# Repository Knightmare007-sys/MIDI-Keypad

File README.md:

# MIDI-Keypad
A small controller with keys that does not make sound itself instead it sends messages to computer or phone which produces sound . It uses EC11 Rotary encoder (turning the knob creates signals which the microncontroller reads to track rotation which is perfect for tasks like changing volume etc ), a waveshare esp32 s3 zero for capacitive touch (the brain of the board), 2 bourns slide potentiometers and some  low profile switches ( when u press them down they close the circuit at a specific matrix coordinate).
This repository includes the schematics and pcb design of the MIDI keypad along with images showing zero errors , and images of it in a 3d view.

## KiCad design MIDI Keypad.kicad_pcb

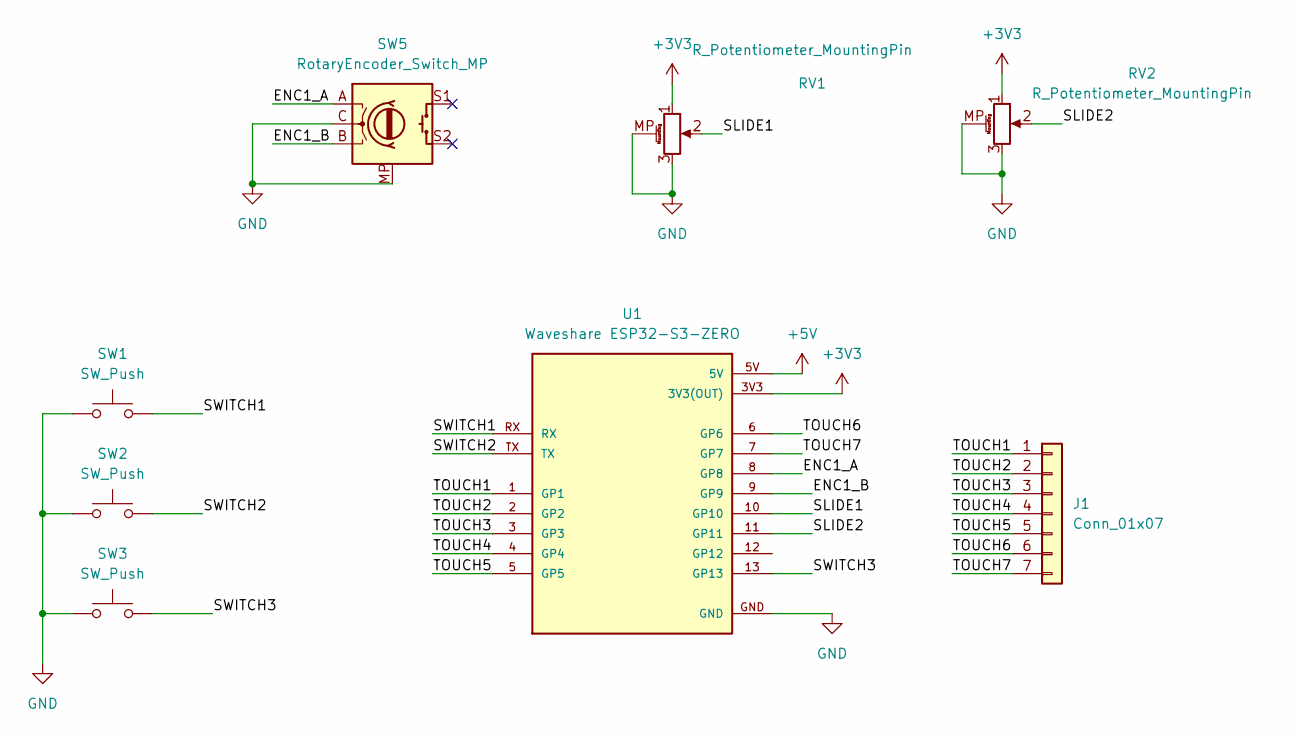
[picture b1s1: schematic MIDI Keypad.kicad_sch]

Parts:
J1: Conn_01x07; capacitative keys
RV1, RV2: R_Potentiometer_MountingPin; Potentiometer_Bourns_PTA1543_Single_Slide
SW1, SW2, SW3: SW_Push; Kailh Choc Low-Profile Switches
SW5: RotaryEncoder_Switch_MP; RotaryEncoder_Alps_EC11E-Switch_Vertical_H20mm
U1: Waveshare ESP32-S3-ZERO; Waveshare ESP32-S3-Zero; PARTREV NA

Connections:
+3V3: RV1.1, RV2.1, U1.3V3 (3V3(OUT))
+5V: U1.5V
/ENC1_A: SW5.A, U1.8 (GP8)
/ENC1_B: SW5.B, U1.9 (GP9)
/SLIDE1: RV1.2, U1.10 (GP10)
/SLIDE2: RV2.2, U1.11 (GP11)
/SWITCH1: SW1.2, U1.RX
/SWITCH2: SW2.2, U1.TX
/SWITCH3: SW3.2, U1.13 (GP13)
/TOUCH1: J1.1, U1.1 (GP1)
/TOUCH2: J1.2, U1.2 (GP2)
/TOUCH3: J1.3, U1.3 (GP3)
/TOUCH4: J1.4, U1.4 (GP4)
/TOUCH5: J1.5, U1.5 (GP5)
/TOUCH6: J1.6, U1.6 (GP6)
/TOUCH7: J1.7, U1.7 (GP7)
GND: RV1.3, RV1.MP (MountPin), RV2.3, RV2.MP (MountPin), SW1.1, SW2.1, SW3.1, SW5.C, SW5.MP, U1.GND

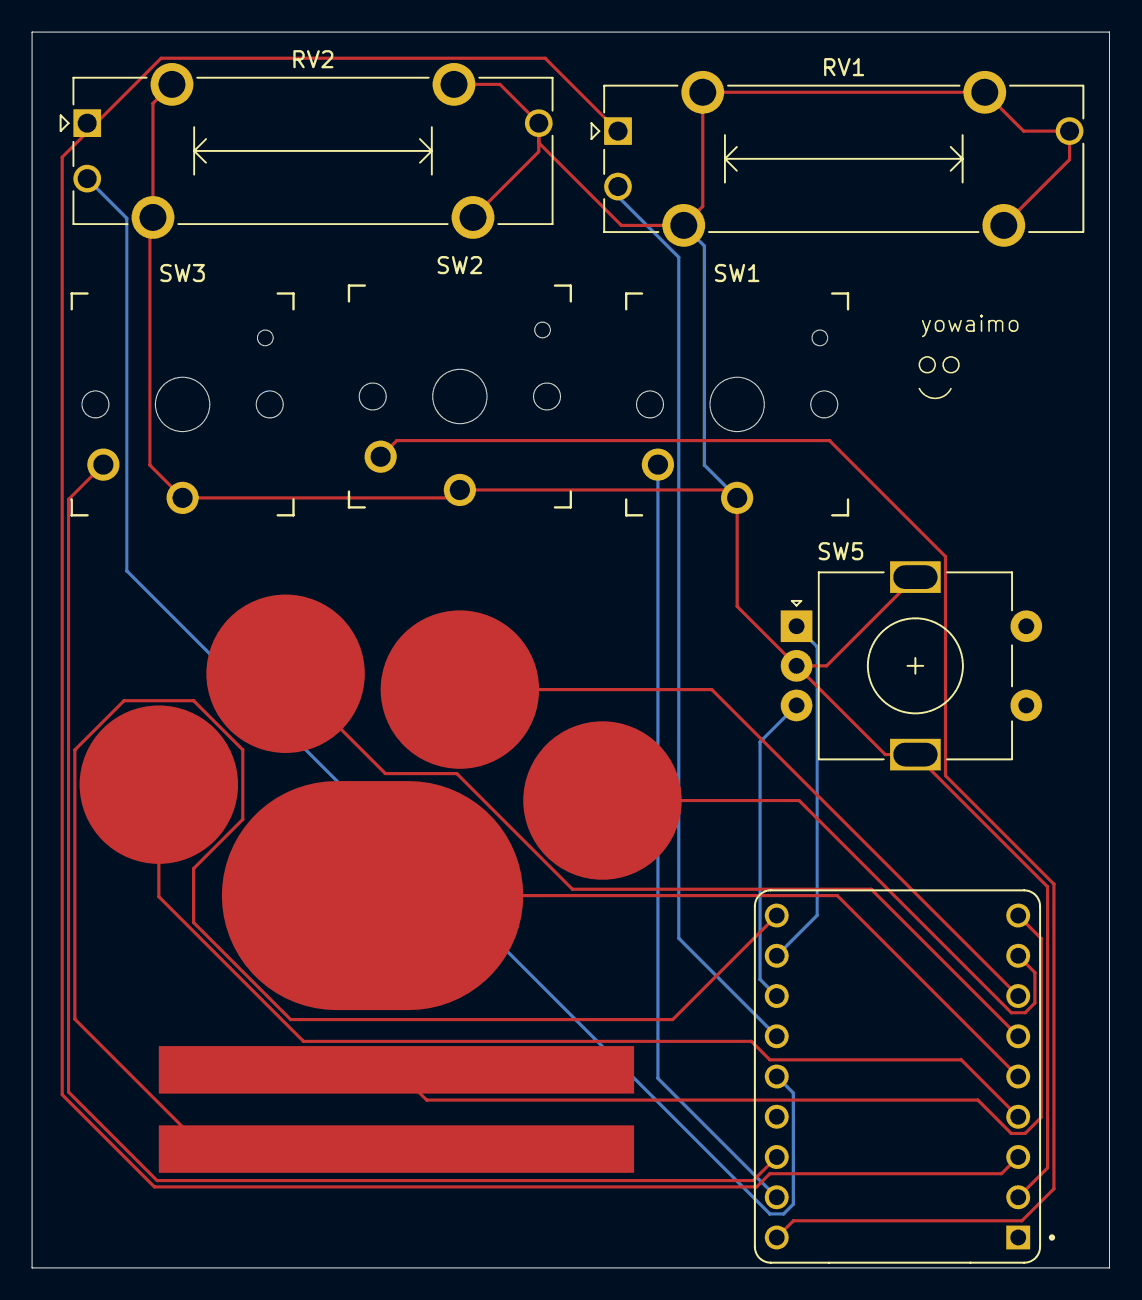
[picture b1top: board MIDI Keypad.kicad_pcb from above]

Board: 2 copper layers, 68.0 x 78.0 mm, 8 parts (0 on the bottom side), 16 nets.

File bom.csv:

Designator,Footprint,Quantity,Value,LCSC Part #
J1,capacitative keys,1,Conn_01x07,
"RV1, RV2",Potentiometer_Bourns_PTA1543_Single_Slide,2,R_Potentiometer_MountingPin,
"SW1, SW2, SW3",Kailh Choc Low-Profile Switches,3,SW_Push,
SW5,RotaryEncoder_Alps_EC11E-Switch_Vertical_H20mm,1,RotaryEncoder_Switch_MP,
U1,Waveshare ESP32-S3-Zero,1,Waveshare ESP32-S3-ZERO,
